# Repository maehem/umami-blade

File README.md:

# umami-blade
Handheld JavaFX Gaming Platform

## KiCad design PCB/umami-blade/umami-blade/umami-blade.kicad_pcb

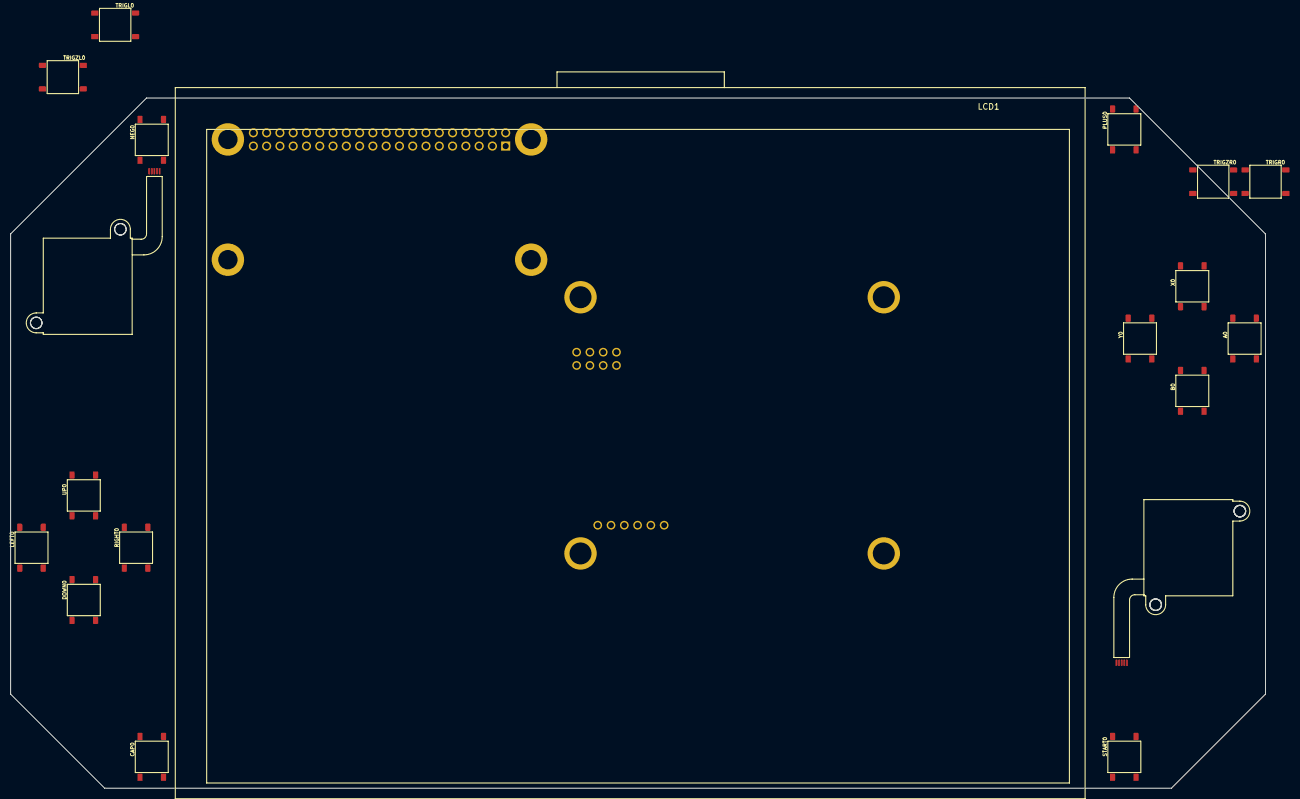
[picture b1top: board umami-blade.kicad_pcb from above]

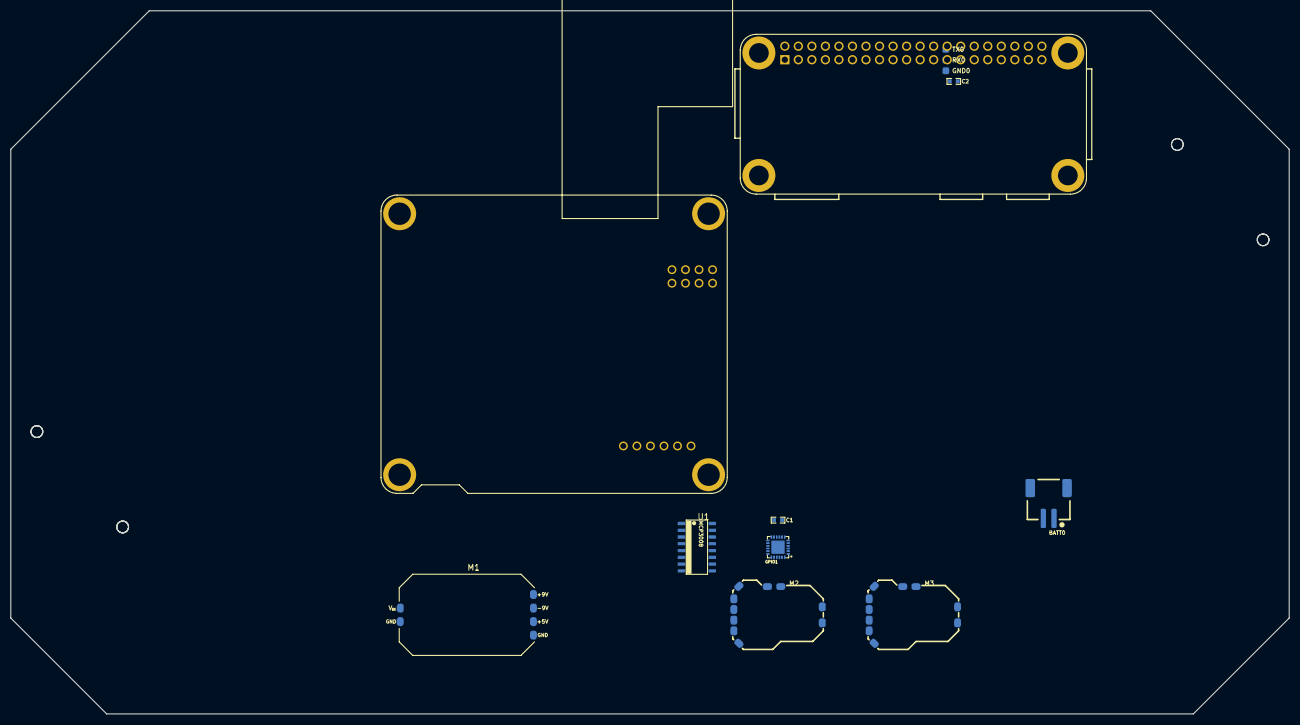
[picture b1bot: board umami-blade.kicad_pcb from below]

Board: 2 copper layers, 240.0 x 132.0 mm, 36 parts (13 on the bottom side), 33 nets, no tracks yet.

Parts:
@HOLE0, @HOLE1, @HOLE2, @HOLE3: (no value)
A0: Tact. Sw.; B3FS
B0: Tact. Sw.; B3FS
BATT0: 2-pin, RA, SMT; S2B-PH-SM4-
C1, C2: 0.1uF; 0603-CAP
CAP0: Tact. Sw.; B3FS
DOWN0: Tact. Sw.; B3FS
GND0: PADSMD-050X050; SMD-050X050
GPIO1: XRA1405; QFN-24
JOY1, JOY2: NINTENDO-JOYCON
LCD1: TFT LCD; PIMORONI_PIM372
LEFT0: Tact. Sw.; B3FS
M1: 0128A
M2, M3: Class-D, 16W; 0123A
MOD1: PIMORONI-LCD-CONTROLLER
NEG0: Tact. Sw.; B3FS
PI1: Pi 2W; PI-ZERO-2W
PLUS0: Tact. Sw.; B3FS
RIGHT0: Tact. Sw.; B3FS
RX0: PADSMD-050X050; SMD-050X050
START0: Tact. Sw.; B3FS
TRIGL0: Tact. Sw.; B3FS
TRIGR0: Tact. Sw.; B3FS
TRIGZL0: Tact. Sw.; B3FS
TRIGZR0: Tact. Sw.; B3FS
TX0: PADSMD-050X050; SMD-050X050
U1: MCP3008; SO16
UP0: Tact. Sw.; B3FS
X0: Tact. Sw.; B3FS
Y0: Tact. Sw.; B3FS

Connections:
+3.3V: C1.1, C2.1, GPIO1.21, GPIO1.23, JOY1.1, JOY2.1, PI1.1, U1.15, U1.16
+5V: M1.5V, MOD1.5V, PI1.2, PI1.4
A: A0.1, A0.2, GPIO1.16
B: B0.1, B0.2, GPIO1.14
CAP: CAP0.1, CAP0.2, GPIO1.8
DOWN: DOWN0.1, DOWN0.2, GPIO1.5
GND: A0.3, A0.4, B0.3, B0.4, BATT0.2, C1.2, C2.2, CAP0.3, CAP0.4, DOWN0.3, DOWN0.4, GND0.1, GPIO1.9, GPIO1.PAD, JOY1.4, JOY2.4, LEFT0.3, LEFT0.4, M1.GNDI, M1.GNDO, M2.GND, M2.GND2, M3.GND, M3.GND2, MOD1.GND@I2S, MOD1.GND@MENU, NEG0.3, NEG0.4, PI1.6, PI1.9, PI1.14, PI1.20, PI1.25, PI1.30, PI1.34, PI1.39, PLUS0.3, PLUS0.4, RIGHT0.3, RIGHT0.4, START0.3, START0.4, TRIGL0.3, TRIGL0.4, TRIGR0.3, TRIGR0.4, TRIGZL0.3, TRIGZL0.4, TRIGZR0.3, TRIGZR0.4, U1.9, U1.14, UP0.3, UP0.4, X0.3, X0.4, Y0.3, Y0.4
LEFT: GPIO1.6, LEFT0.1, LEFT0.2
unnamed: JOY1.3, U1.2
unnamed: JOY1.2, U1.1
unnamed: JOY1.5, U1.3
unnamed: JOY2.2, U1.5
unnamed: JOY2.5, U1.7
unnamed: JOY2.3, U1.6
NEG: GPIO1.3, NEG0.1, NEG0.2
PLUS: GPIO1.12, PLUS0.1, PLUS0.2
RIGHT: GPIO1.7, RIGHT0.1, RIGHT0.2
RX: PI1.10, RX0.1
SPI_CLK: GPIO1.19, PI1.23, U1.13
SPI_DI: GPIO1.24, PI1.19, U1.11
SPI_DO: GPIO1.20, PI1.21, U1.12
START: GPIO1.17, START0.1, START0.2
TRIGL: GPIO1.1, TRIGL0.1, TRIGL0.2
TRIGR: GPIO1.10, TRIGR0.1, TRIGR0.2
TRIGZL: GPIO1.2, TRIGZL0.1, TRIGZL0.2
TRIGZR: GPIO1.11, TRIGZR0.1, TRIGZR0.2
TX: PI1.8, TX0.1
UP: GPIO1.4, UP0.1, UP0.2
X: GPIO1.13, X0.1, X0.2
Y: GPIO1.15, Y0.1, Y0.2
~BTN_CS: GPIO1.18, PI1.24
~BTN_IRQ: GPIO1.22, PI1.22
~JOY_CS: PI1.26, U1.10

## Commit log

2022-05-17 PCB files added.
2022-09-30 progress
2022-10-02 Create KiCAD version of PCB
2026-01-14 Work in progress check-in.
